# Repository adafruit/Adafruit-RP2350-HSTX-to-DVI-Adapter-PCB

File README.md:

## Adafruit RP2350 22-pin FPC HSTX to DVI Adapter for HDMI Displays PCB

<a href="http://www.adafruit.com/products/6055"><br/>
Click here to purchase one from the Adafruit shop</a>

PCB files for the Adafruit RP2350 22-pin FPC HSTX to DVI Adapter for HDMI Displays. 

Format is EagleCAD schematic and board layout
* https://www.adafruit.com/product/6055

### Description

You may have noticed that our RP2350 Feather has an FPC output connector on the end for accessing the HSTX (High Speed Transmission) peripheral. This new capability, not available on the RP2040, is specifically designed to allow the RP2350 chip drive DVI displays really easily! Historically you could use DVI on the RP2040 by mashing together some overclocking and a lot of PIO - it works but its quite hacky. The HSTX peripheral is streamlined, and doesn't require PIO or overclocking and there's a lot more RAM on the RP2350.

If you want to try out HSTX to drive an HDMI monitor or display, this dongle is what you need to take HSTX out and give you a connector with proper level shifting and signal conditioning. Simply connect a 22 pin FPC cable between the Feather RP2350 and Adafruit RP2350 22-pin FPC HSTX to DVI Adapter for HDMI Displays then load DVI output code. In CircuitPython, we have support for 320x240 pixels at 16-bit color, which gets pixel doubled to 640x480. Or, if you're willing to cut some colorspace to save RAM, you can get true 640x480 resolution at 4 / 8 bit color, or 1 / 2 bit grayscale.

The eight HSTX lines are connected to the differential Clock (IO #14 & 15), Lane0 (#18, 19), Lane1 (#16, #17), and Lane2 (#12, #13) connections. I2C is connected as well so you can read the display EEPROM. Hot-plug-detect is connected to IO #11 on the Feather, but can be disconnected by cutting a jumper on the bottom. Ditto for CEC which we connect by default to IO #10.

Each order comes with one DVI adapter board. 22-pin FPC cable is not included, so be sure to get one too!

### License

Adafruit invests time and resources providing this open source design, please support Adafruit and open-source hardware by purchasing products from [Adafruit](https://www.adafruit.com)!

Designed by Limor Fried/Ladyada for Adafruit Industries.

Creative Commons Attribution/Share-Alike, all text above must be included in any redistribution. 
See license.txt for additional details.

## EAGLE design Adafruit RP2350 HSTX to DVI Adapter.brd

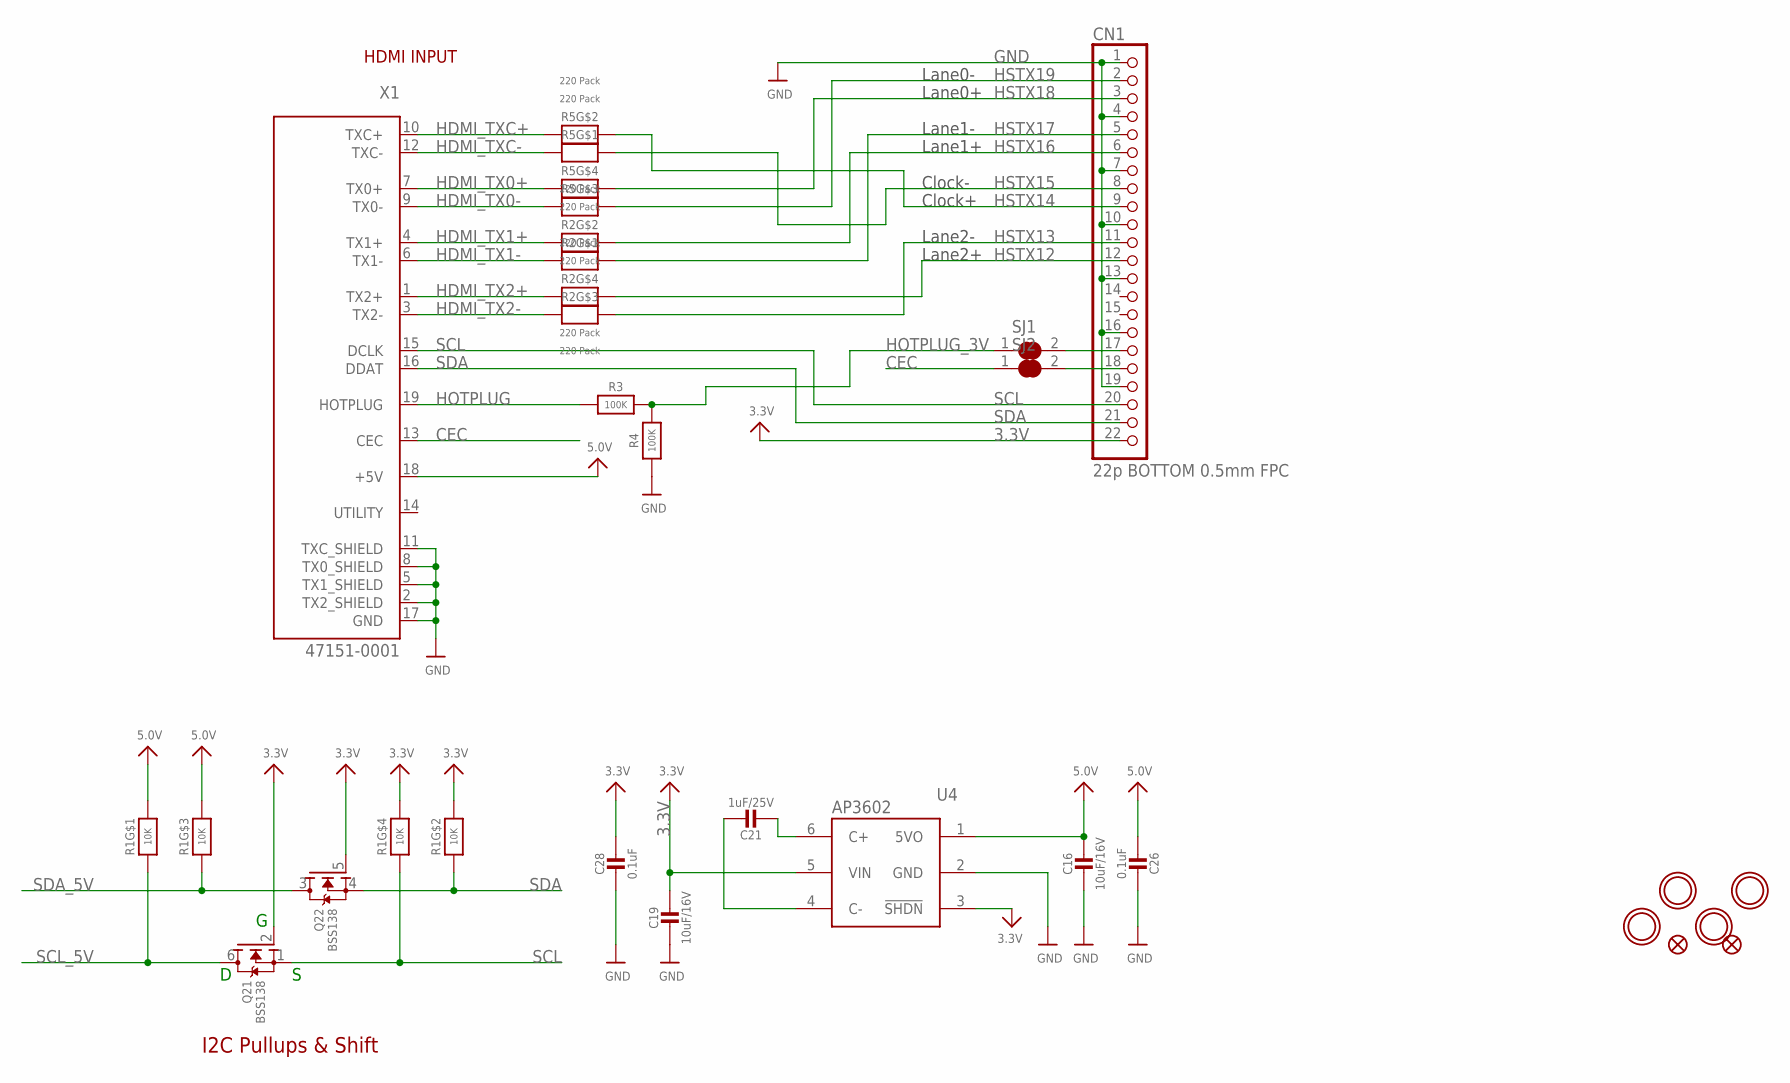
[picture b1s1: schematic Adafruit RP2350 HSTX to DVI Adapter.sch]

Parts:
C16, C19: 10uF/16V; 0805-NO
C21: 1uF/25V; 0603-NO
C26, C28: 0.1uF; 0603-NO
CN1: 22p BOTTOM 0.5mm FPC; FPC_22PIN
FID1, FID2: FIDUCIAL_1MM
Q2: BSS138; SOT363
R1: 10K; RESPACK_4X0603
R2, R5: 220 Pack; RESPACK_4X0603
R3, R4: 100K; 0603-NO
SJ1, SJ2: SOLDERJUMPER_CLOSED; SOLDERJUMPER_CLOSEDWIRE
U4: AP3602; SOT23-6
U$2, U$3, U$5, U$7: MOUNTINGHOLE2.5; MOUNTINGHOLE_2.5_PLATED
X1: 47151-0001; HDMI_MOLEX_47151-0001

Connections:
3.3V: C19.1, C28.1, CN1.22, Q2.2 (G), Q2.5 (G), R1.5 (2), R1.7 (2), U4.3 (!SHDN), U4.5 (VIN)
5.0V: C16.1, C26.2, R1.6 (2), R1.8 (2), U4.1 (5VO), X1.18 (+5V)
CEC: SJ2.1, X1.13 (CEC)
GND: C16.2, C19.2, C26.1, C28.2, CN1.1, CN1.4, CN1.7, CN1.10, CN1.13, CN1.16, CN1.19, R4.1, U4.2 (GND), X1.2 (TX2_SHIELD), X1.5 (TX1_SHIELD), X1.8 (TX0_SHIELD), X1.11 (TXC_SHIELD), X1.17 (GND), X1.P$1 (GND), X1.P$2 (GND), X1.P$3 (GND), X1.P$4 (GND)
HDMI_TX0+: R5.4 (1), X1.7 (TX0+)
HDMI_TX0-: R5.3 (1), X1.9 (TX0-)
HDMI_TX1+: R2.2 (1), X1.4 (TX1+)
HDMI_TX1-: R2.1, X1.6 (TX1-)
HDMI_TX2+: R2.4 (1), X1.1 (TX2+)
HDMI_TX2-: R2.3 (1), X1.3 (TX2-)
HDMI_TXC+: R5.2 (1), X1.10 (TXC+)
HDMI_TXC-: R5.1, X1.12 (TXC-)
HOTPLUG: R3.1, X1.19 (HOTPLUG)
HOTPLUG_3V: R3.2, R4.2, SJ1.1
HSTX12: CN1.12, R2.5 (2)
HSTX13: CN1.11, R2.6 (2)
HSTX14: CN1.9, R5.7 (2)
HSTX15: CN1.8, R5.8 (2)
HSTX16: CN1.6, R2.7 (2)
HSTX17: CN1.5, R2.8 (2)
HSTX18: CN1.3, R5.5 (2)
HSTX19: CN1.2, R5.6 (2)
unnamed: CN1.17, SJ1.2
unnamed: CN1.18, SJ2.2
unnamed: C21.1, U4.4 (C-)
unnamed: C21.2, U4.6 (C+)
SCL: CN1.20, Q2.1 (S), R1.4 (1), X1.15 (DCLK)
SCL_5V: Q2.6 (D), R1.1
SDA: CN1.21, Q2.4 (S), R1.2 (1), X1.16 (DDAT)
SDA_5V: Q2.3 (D), R1.3 (1)

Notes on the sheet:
HDMI INPUT
I2C Pullups & Shift
Lane0-
Lane0+
Lane1-
Lane1+
Clock-
Clock+
Lane2-
Lane2+

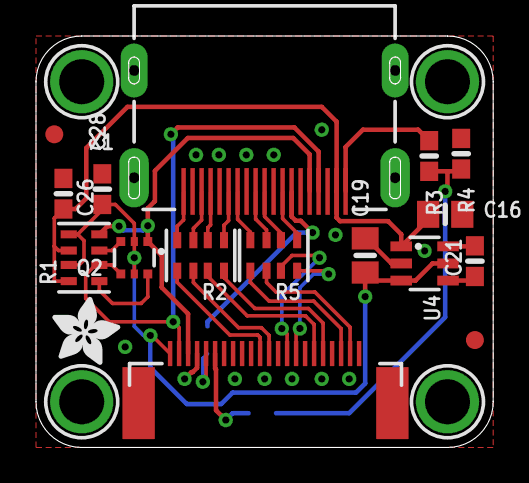
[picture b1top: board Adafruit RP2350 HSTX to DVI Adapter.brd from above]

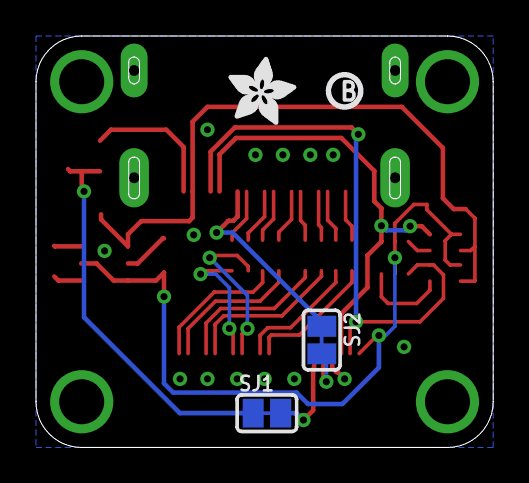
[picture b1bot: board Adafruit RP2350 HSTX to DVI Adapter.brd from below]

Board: 2 copper layers, 25.4 x 22.9 mm, 30 parts (7 on the bottom side), 30 nets.

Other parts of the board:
PLABEL0: PLABEL0
PLABEL1: PLABEL1
PLABEL2: PLABEL2
PLABEL3: PLABEL3
PLABEL4: PLABEL4
U$4, U$21: ADAFRUIT_3.5MM
U$6: PCBFEAT-REV-040

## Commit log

2024-10-02 cookiecutter

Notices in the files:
parts and their libraries:
microbuilder: This work is placed in the public domain, and may be freely used for commercial and non-commercial work with the following conditions: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
